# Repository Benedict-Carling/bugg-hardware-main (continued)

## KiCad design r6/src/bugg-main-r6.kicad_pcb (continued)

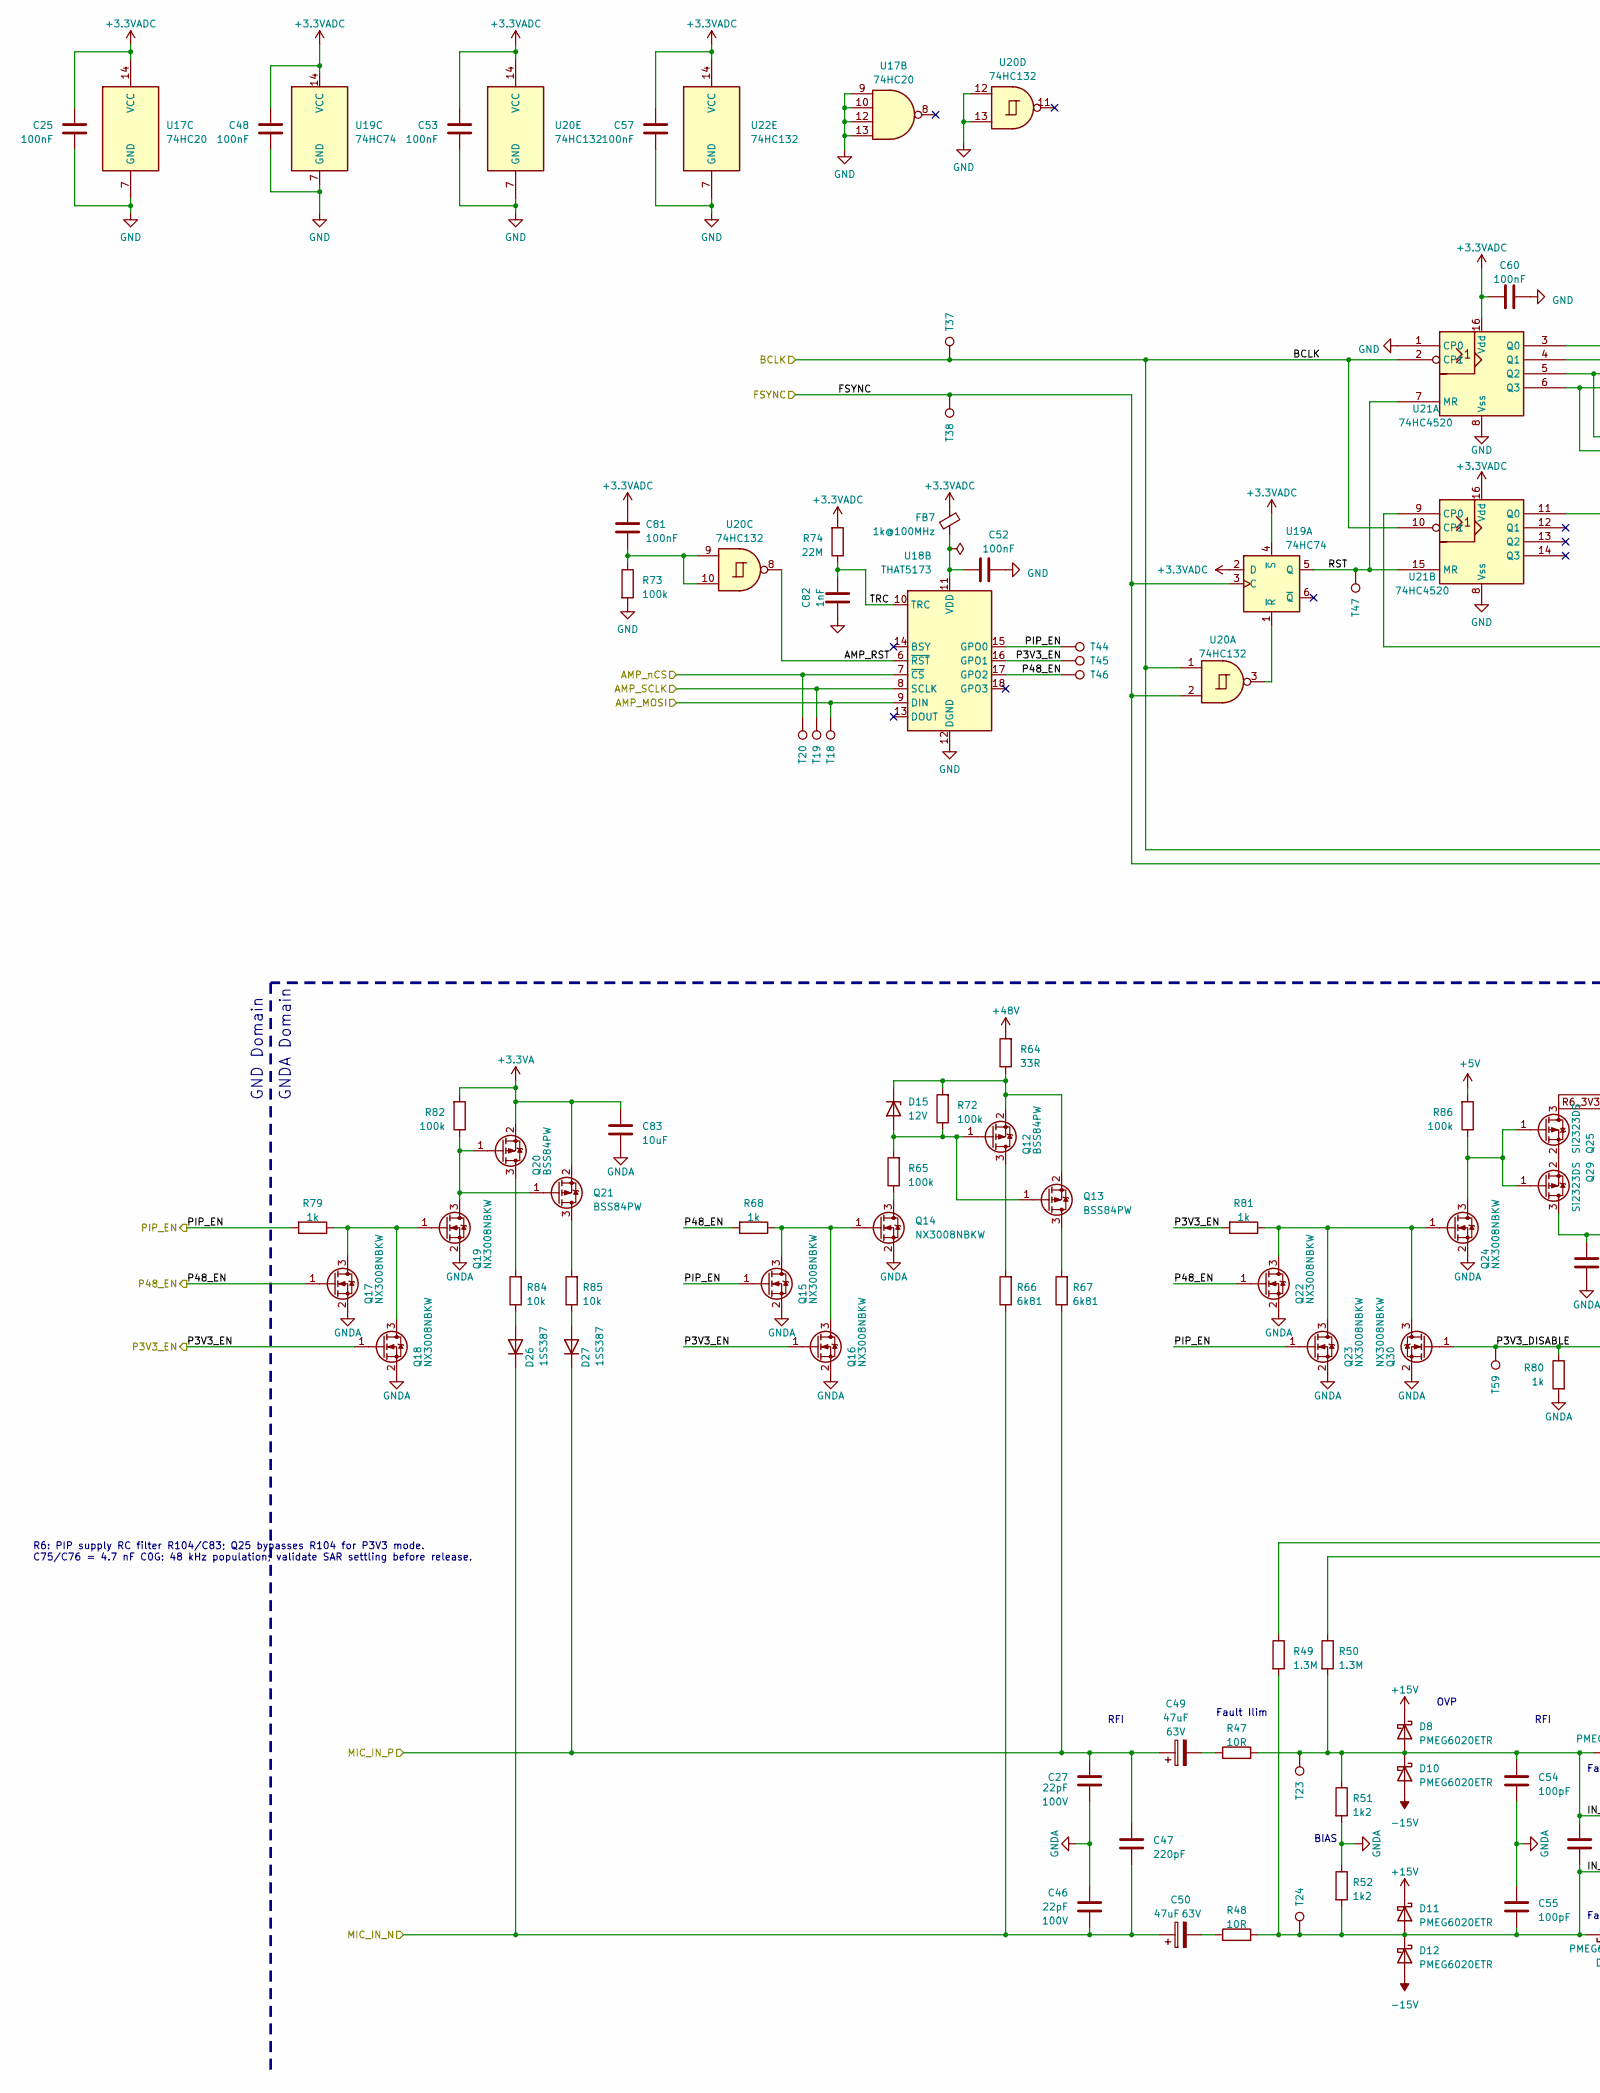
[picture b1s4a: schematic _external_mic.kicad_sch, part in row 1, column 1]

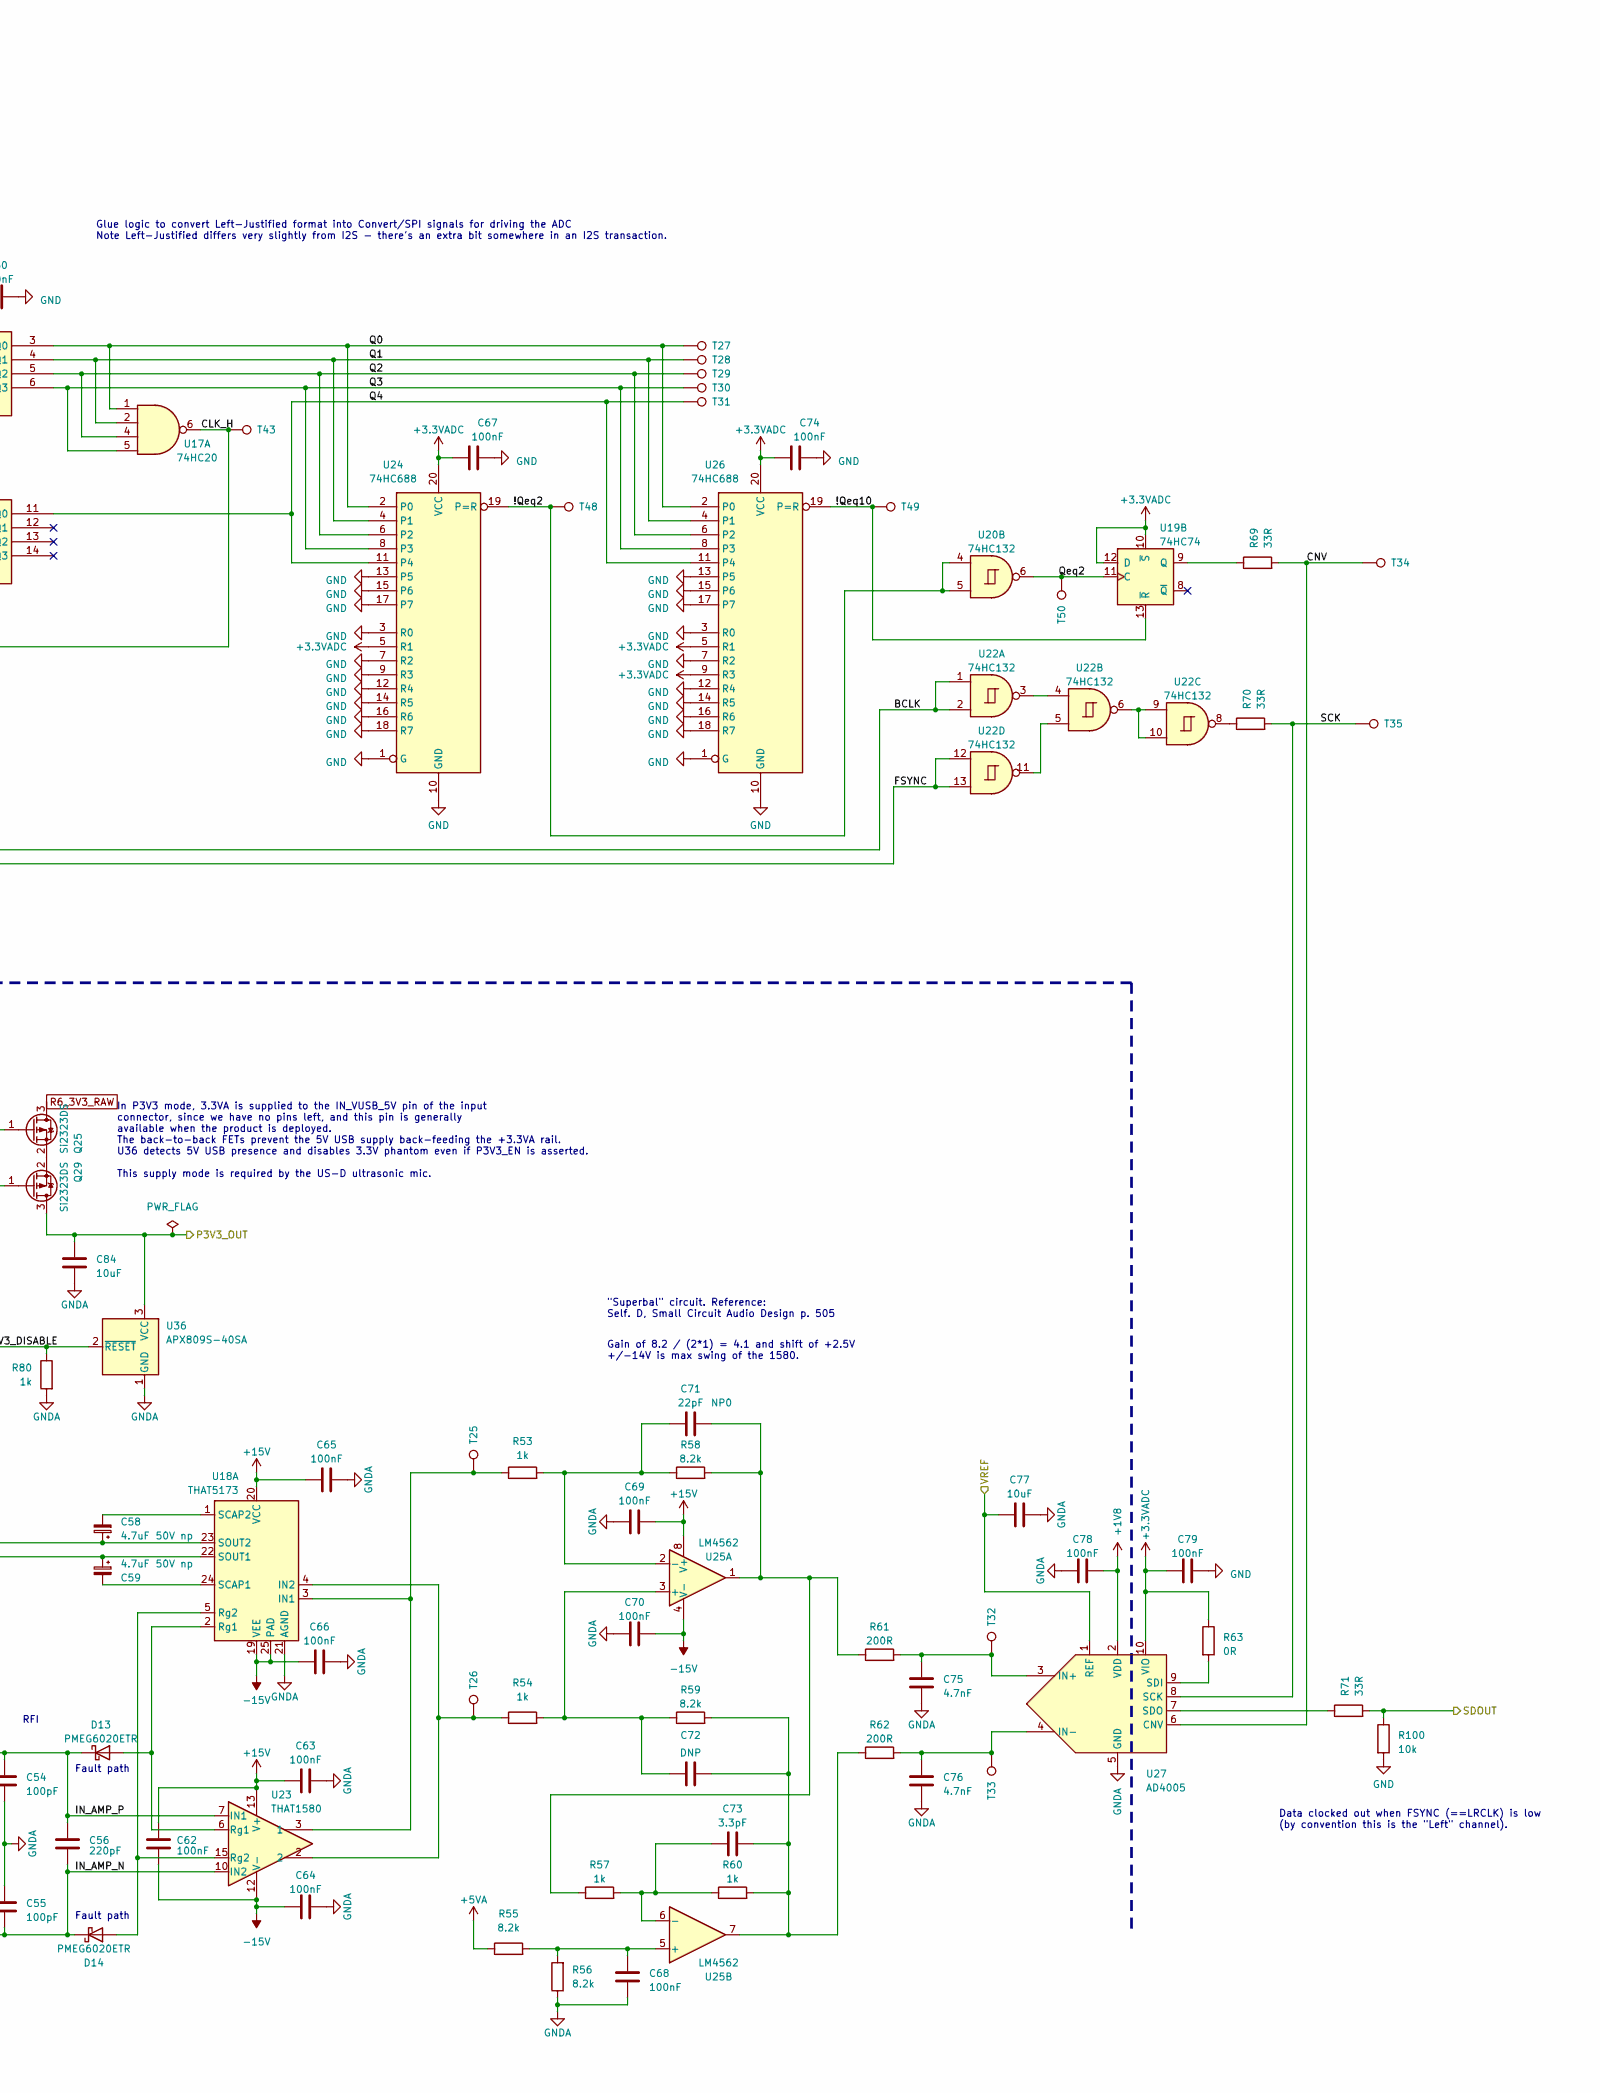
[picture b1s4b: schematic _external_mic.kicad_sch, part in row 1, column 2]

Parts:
C25, C48, C52, C53, C57, C60, C62, C63, C64, C65, C66, C67, C68, C69, C70, C74, C78, C79, C81: 100nF; C_0402_1005Metric; Voltage 50V; MPN GRM155R71H104KE14D; Mouser 81-GRM155R71H104KE4D
C27, C46, C71: 22pF; C_0402_1005Metric; Voltage 100V
C47, C56: 220pF; C_0402_1005Metric
C49, C50: 47uF; CP_Elec_8x10.5; Voltage 63V; MPN EMVH630ADA470MHA0G; Mouser 565-4268-1-ND
C54, C55: 100pF; C_0402_1005Metric
C58, C59: 4.7uF; CP_Elec_5x5.4; Voltage 50V np; MPN 865250642008; Mouser 710-865250642008
C72: DNP; C_0402_1005Metric
C73: 3.3pF; C_0402_1005Metric
C75, C76: 4.7nF; C_0402_1005Metric; MPN GRM1555C1H472JE01D
C77, C83, C84: 10uF; C_0603_1608Metric; Voltage 6.3V; MPN CL10A106MQ8NNNC; Mouser 187-CL10A106MQ8NNNC
C82: 1nF; C_0402_1005Metric
D8, D10, D11, D12, D13, D14: PMEG6020ETR; Nexperia_CFP3_SOD-123W; MPN PMEG6020ETR,115; Digikey 1727-1347-1-ND
D15: 12V; D_SOD-123; MPN BZT52C12-13-F; Digikey BZT52C1213-FDIDKR-ND
D26, D27: 1SS387; D_SOD-523; MPN 1SS387,L3F; Mouser 757-1SS387L3F
FB7: 1k@100MHz; L_0603_1608Metric; MPN BLM18KG102SN1D; Digikey 490-17349-1-ND
Q12, Q13, Q20, Q21: BSS84PW; SOT-323_SC-70; MPN BSS84PW; Mouser 726-BSS84PWH6327XTSA
Q14, Q15, Q16, Q17, Q18, Q19, Q22, Q23, Q24, Q30: NX3008NBKW; SOT-323_SC-70; MPN NX3008NBKW; Digikey 1727-1280-6-ND
Q25, Q29: Si2323DS; SOT-23; MPN SI2323DS-T1
R47, R48: 10R; R_1206_3216Metric; Tolerance 0.1%
R49, R50: 1.3M; R_0402_1005Metric
R51, R52: 1k2; R_0402_1005Metric; Tolerance 0.1% thin film; MPN ERA-2AEB122X; Mouser 667-ERA-2AEB122X
R53, R54, R57, R60: 1k; R_0402_1005Metric; Tolerance 0.1% thin film; MPN ERA-2AEB102X; Mouser 667-ERA-2AEB102X
R55, R56, R58, R59: 8.2k; R_0402_1005Metric; Tolerance 0.1% thin film; MPN ERA-2AEB822X; Mouser 667-ERA-2AEB822X
R61, R62: 200R; R_0402_1005Metric; Tolerance 0.1% thin film; MPN ERA-2AEB201X; Mouser 667-ERA-2AEB201X
R63: 0R; R_0402_1005Metric
R64, R69, R70, R71: 33R; R_0402_1005Metric
R65, R72, R73, R82, R86: 100k; R_0402_1005Metric
R66, R67: 6k81; R_1206_3216Metric
R68, R79, R80, R81: 1k; R_0402_1005Metric
R74: 22M; R_0402_1005Metric
R84, R85, R100: 10k; R_0402_1005Metric
T18, T19, T20, T23, T24, T25, T26, T27, T28, T29, T30, T31, T32, T33, T34, T35, T37, T38, T43, T44, T45, T46, T47, T48, T49, T50, T59: TestPoint_Pad_D1.0mm
U17: 74HC20; TSSOP-14_4.4x5mm_P0.65mm; MPN 74HC20PW; Mouser 771-HC20PW118
U18: THAT5173; QFN-24-1EP_5x5mm_P0.65mm_EP3.4x3.4mm_ThermalVias; MPN 5173N24-U; Mouser 887-5173N24-U
U19: 74HC74; TSSOP-14_4.4x5mm_P0.65mm; MPN 74HC74PW; Mouser 771-74HC74PW-T
U20, U22: 74HC132; TSSOP-14_4.4x5mm_P0.65mm; MPN 74HC132PW; Mouser 771-74HC132PW-T
U21: 74HC4520; TSSOP-16_4.4x5mm_P0.65mm; MPN 74HC4520PW; Mouser 771-HC4520PW118
U23: THAT1580; QFN-16-1EP_4x4mm_P0.65mm_EP2.1x2.1mm_ThermalVias; MPN 1580N16-U; Mouser 887-1580N16-U
U24, U26: 74HC688; TSSOP-20_4.4x6.5mm_P0.65mm; MPN 74HC688PW; Mouser 771-HC688PW118
U25: LM4562; SOIC-8_3.9x4.9mm_P1.27mm; MPN LM4562MA; Mouser 926-LM4562MAX/NOPB
U27: AD4005; MSOP-10_3x3mm_P0.5mm; MPN AD4005BRMZ; Mouser 584-AD4005BRMZ
U36: APX809S-40SA; SOT-23; MPN APX809S-40SA; Mouser 621-APX809S-40SA-7

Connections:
+1V8: C78.2, U27.2 (VDD); also elsewhere on the board
+3.3VA: C83.2, Q20.2 (S), Q21.2 (S), R82.2; also elsewhere on the board
+3.3VADC: C25.2, C48.2, C53.2, C57.2, C60.2, C67.2, C74.2, C79.2, C81.1, FB7.2, R63.1, R74.2, U17.14 (VCC), U19.2 (D), U19.4 (~S), U19.10 (~S), U19.12 (D), U19.14 (VCC), U20.14 (VCC), U21.16 (Vdd), U22.14 (VCC), U24.5 (R1), U24.20 (VCC), U26.5 (R1), U26.9 (R3), U26.20 (VCC), U27.10 (VIO); also elsewhere on the board
+5V: R86.2; also elsewhere on the board
+5VA: R55.1; also elsewhere on the board
+15V: C62.1, C63.2, C65.2, C69.2, D8.1 (K), D11.1 (K), U18.20 (VCC), U23.13 (V+), U25.8 (V+); also elsewhere on the board
+48V: R64.2; also elsewhere on the board
-15V: C62.2, C64.1, C66.2, C70.1, D10.2 (A), D12.2 (A), U18.19 (VEE), U18.25 (PAD), U23.12 (V-), U23.17 (V-), U25.4 (V-); also elsewhere on the board
/48V_EN: Q17.1 (G), Q22.1 (G), R68.2, T46.1, U18.17 (GPO2); also elsewhere on the board
/BCLK: T37.1, U20.1, U21.2 (CP1), U21.10 (CP1), U22.1, U22.2; also elsewhere on the board
/External Microphone Interface/!Qeq2: T48.1, U20.4, U20.5, U24.19 (P=R)
/External Microphone Interface/!Qeq10: T49.1, U19.13 (~R), U26.19 (P=R)
/External Microphone Interface/AMP_MOSI: T18.1, U18.9 (DIN); also elsewhere on the board
/External Microphone Interface/AMP_RST: U18.6 (~RST), U20.8
/External Microphone Interface/AMP_SCLK: T19.1, U18.8 (SCLK); also elsewhere on the board
/External Microphone Interface/AMP_nCS: T20.1, U18.7 (~CS); also elsewhere on the board
/External Microphone Interface/CLK_H: T43.1, U17.6, U21.9 (CP0)
/External Microphone Interface/CNV: R69.2, T34.1, U27.6 (CNV)
/External Microphone Interface/IN_AMP_N: C55.1, C56.1, D11.2 (A), D12.1 (K), D14.1 (K), R48.2, R49.2, R52.2, T24.1, U23.10 (IN2)
/External Microphone Interface/IN_AMP_P: C54.2, C56.2, D8.2 (A), D10.1 (K), D13.1 (K), R47.2, R50.2, R51.1, T23.1, U23.7 (IN1)
/External Microphone Interface/P3V3_DISABLE: Q30.1 (G), R80.1, T59.1, U36.2 (~RESET)
/External Microphone Interface/P3V3_EN: Q16.1 (G), Q18.1 (G), R81.2, T45.1, U18.16 (GPO1)
/External Microphone Interface/PIP_EN: Q15.1 (G), Q23.1 (G), R79.2, T44.1, U18.15 (GPO0)
/External Microphone Interface/Q0: T27.1, U17.1, U21.3 (Q0), U24.2 (P0), U26.2 (P0)
/External Microphone Interface/Q1: T28.1, U17.2, U21.4 (Q1), U24.4 (P1), U26.4 (P1)
/External Microphone Interface/Q2: T29.1, U17.4, U21.5 (Q2), U24.6 (P2), U26.6 (P2)
/External Microphone Interface/Q3: T30.1, U17.5, U21.6 (Q3), U24.8 (P3), U26.8 (P3)
/External Microphone Interface/Q4: T31.1, U21.11 (Q0), U24.11 (P4), U26.11 (P4)
/External Microphone Interface/Qeq2: T50.1, U19.11 (C), U20.6
/External Microphone Interface/RST: T47.1, U19.5 (Q), U21.7 (MR), U21.15 (MR)
/External Microphone Interface/SCK: R70.2, T35.1, U27.8 (SCK)
/External Microphone Interface/TRC: C82.2, R74.1, U18.10 (TRC)
/FSYNC: T38.1, U19.3 (C), U20.2, U22.12, U22.13; also elsewhere on the board
/MIC_IN_N: C46.1, C47.1, C50.1, D26.1 (K), R66.1; also elsewhere on the board
/MIC_IN_P: C27.2, C47.2, C49.1, D27.1 (K), R67.1; also elsewhere on the board
/P3V3_OUT: C84.2, Q29.3 (D), U36.3 (VCC); also elsewhere on the board
/SDOUT_EXT_MIC: R71.2, R100.1; also elsewhere on the board
/VREF: C77.2, U27.1 (REF); also elsewhere on the board
GND: C25.1, C48.1, C52.1, C53.1, C57.1, C60.1, C67.1, C74.1, C79.1, C82.1, R73.2, R100.2, U17.7 (GND), U17.9, U17.10, U17.12, U17.13, U18.12 (DGND), U19.7 (GND), U20.7 (GND), U20.12, U20.13, U21.1 (CP0), U21.8 (Vss), U22.7 (GND), U24.1 (G), U24.3 (R0), U24.7 (R2), U24.9 (R3), U24.10 (GND), U24.12 (R4), U24.13 (P5), U24.14 (R5), U24.15 (P6), U24.16 (R6), U24.17 (P7), U24.18 (R7), U26.1 (G), U26.3 (R0), U26.7 (R2), U26.10 (GND), U26.12 (R4), U26.13 (P5), U26.14 (R5), U26.15 (P6), U26.16 (R6), U26.17 (P7), U26.18 (R7); also elsewhere on the board
GNDA: C27.1, C46.2, C54.1, C55.2, C63.1, C64.2, C65.1, C66.1, C68.2, C69.1, C70.2, C75.2, C76.2, C77.1, C78.1, C83.1, C84.1, Q14.2 (S), Q15.2 (S), Q16.2 (S), Q17.2 (S), Q18.2 (S), Q19.2 (S), Q22.2 (S), Q23.2 (S), Q24.2 (S), Q30.2 (S), R51.2, R52.1, R56.1, R80.2, U18.21 (AGND), U27.5 (GND), U36.1 (GND); also elsewhere on the board
unnamed: C49.2, R47.1
unnamed: C50.2, R48.1
unnamed: C71.2, R57.1, R58.2, R61.1, U25.1
unnamed: C72.2, C73.2, R59.2, R60.2, R62.1, U25.7
unnamed: C81.2, R73.1, U20.9, U20.10
unnamed: D13.2 (A), U18.2 (Rg1), U23.6 (Rg1)
unnamed: D14.2 (A), U18.5 (Rg2), U23.15 (Rg2)
unnamed: D15.2 (A), Q12.1 (G), Q13.1 (G), R65.2, R72.1
unnamed: D15.1 (K), Q12.2 (S), Q13.2 (S), R64.1, R72.2
unnamed: D26.2 (A), R84.1
unnamed: D27.2 (A), R85.1
unnamed: Q12.3 (D), R66.2
unnamed: Q13.3 (D), R67.2
unnamed: Q14.3 (D), R65.1
unnamed: Q14.1 (G), Q15.3 (D), Q16.3 (D), R68.1
unnamed: Q17.3 (D), Q18.3 (D), Q19.1 (G), R79.1
unnamed: Q19.3 (D), Q20.1 (G), Q21.1 (G), R82.1
unnamed: Q20.3 (D), R84.2
unnamed: Q21.3 (D), R85.2
unnamed: Q22.3 (D), Q23.3 (D), Q24.1 (G), Q30.3 (D), R81.1
unnamed: Q24.3 (D), Q25.1 (G), Q29.1 (G), R86.1
unnamed: Q25.2 (S), Q29.2 (S)
unnamed: R70.1, U22.8
unnamed: R53.1, T25.1, U18.3 (IN1), U23.3 (1)
unnamed: R54.1, T26.1, U18.4 (IN2), U23.2
unnamed: C59.2, U18.24 (SCAP1)
unnamed: C58.2, U18.1 (SCAP2)
unnamed: C59.1, R50.1, U18.22 (SOUT1)
unnamed: C58.1, R49.1, U18.23 (SOUT2)
unnamed: C52.2, FB7.1, U18.11 (VDD)
unnamed: U19.1 (~R), U20.3
unnamed: R69.1, U19.9 (Q)
unnamed: U22.3, U22.4
unnamed: U22.6, U22.9, U22.10
unnamed: U22.5, U22.11
unnamed: C72.1, R54.2, R59.1, U25.3 (+)
unnamed: C71.1, R53.2, R58.1, U25.2 (-)
unnamed: C68.1, R55.2, R56.2, U25.5 (+)
unnamed: C73.1, R57.2, R60.1, U25.6 (-)
unnamed: C75.1, R61.2, T32.1, U27.3 (IN+)
unnamed: C76.1, R62.2, T33.1, U27.4 (IN-)
unnamed: R63.2, U27.9 (SDI)
unnamed: R71.1, U27.7 (SDO)
R6_3V3_RAW: Q25.3 (D); also elsewhere on the board

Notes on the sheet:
OVP
RFI
Fault path
BIAS
"Superbal" circuit. Reference: Self. D, Small Circuit Audio Design p. 505
Gain of 8.2 / (2*1) = 4.1 and shift of +2.5V +/-14V is max swing of the 1580.
Glue logic to convert Left-Justified format into Convert/SPI signals for driving the ADC Note Left-Justified differs very slightly from I2S - there's an extra bit somewhere in an I2S transaction.
Data clocked out when FSYNC (==LRCLK) is low (by convention this is the "Left" channel).
In P3V3 mode, 3.3VA is supplied to the IN_VUSB_5V pin of the input connector, since we have no pins left, and this pin is generally available when the product is deployed. The back-to-back FETs prevent the 5V USB supply back-feeding the +3.3VA rail. U36 detects 5V USB presence and disables 3.3V pha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
GNDA Domain
Fault Ilim
GND Domain
R6: PIP supply RC filter R104/C83; Q25 bypasses R104 for P3V3 mode. C75/C76 = 4.7 nF C0G: 48 kHz population; validate SAR settling before release.

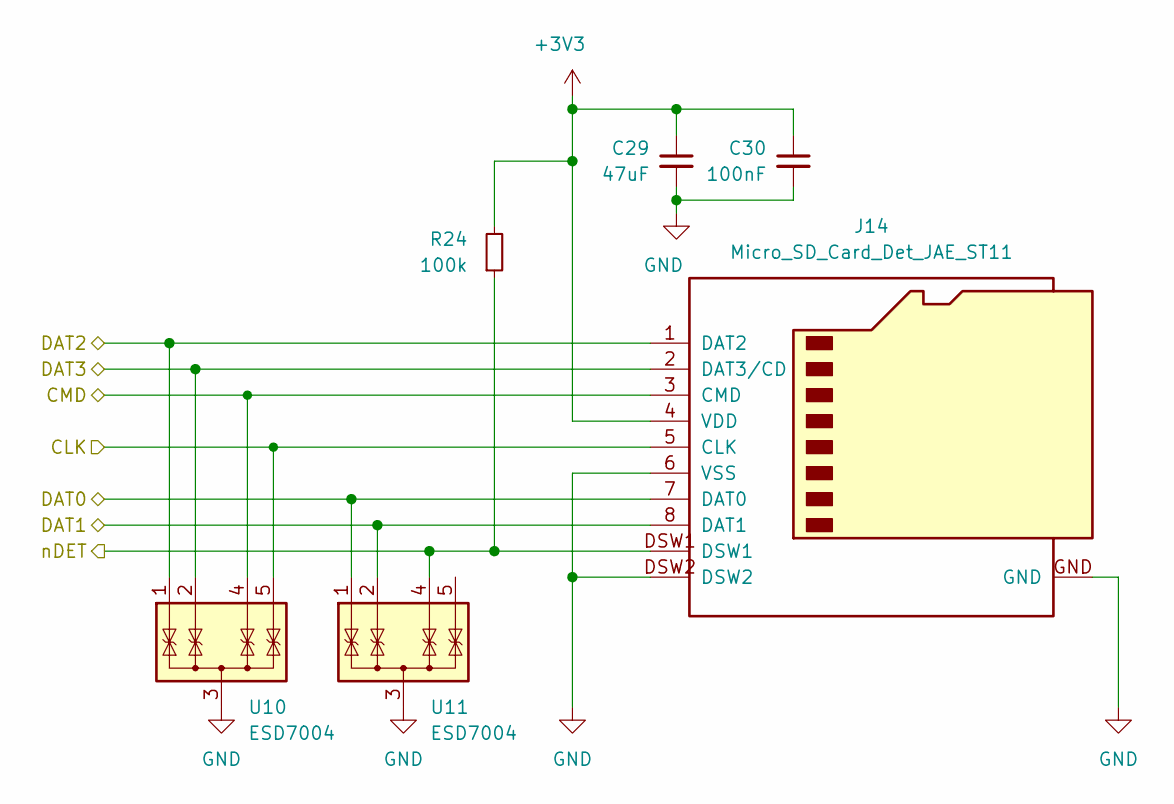
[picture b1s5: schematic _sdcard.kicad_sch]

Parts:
C29: 47uF; C_1206_3216Metric; Voltage 6.3V; MPN GRM31CE70J476ME15L; Mouser 81-GRM31CE70J476ME5L
C30: 100nF; C_0402_1005Metric; Voltage 50V; MPN GRM155R71H104KE14D; Mouser 81-GRM155R71H104KE4D
J14: Micro_SD_Card_Det_JAE_ST11; microSD_JAE_ST11S008V4H; MPN ST11S008V4HR2000; Digikey 670-2695-6-ND
R24: 100k; R_0402_1005Metric
U10, U11: ESD7004; USON-10_2.5x1.0mm_P0.5mm; MPN ESD7004MUTAG; Digikey ESD7004MUTAGOSDKR-ND

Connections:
+3V3: C29.1, C30.1, J14.4 (VDD), R24.2; also elsewhere on the board
/SD_CLK: J14.5 (CLK), U10.5 (IO4), U10.6; also elsewhere on the board
/SD_CMD: J14.3 (CMD), U10.4 (IO3), U10.7; also elsewhere on the board
/SD_DAT0: J14.7 (DAT0), U11.1 (IO1), U11.10; also elsewhere on the board
/SD_DAT1: J14.8 (DAT1), U11.2 (IO2), U11.9; also elsewhere on the board
/SD_DAT2: J14.1 (DAT2), U10.1 (IO1), U10.10; also elsewhere on the board
/SD_DAT3: J14.2 (DAT3/CD), U10.2 (IO2), U10.9; also elsewhere on the board
/SD_nDET: J14.DSW1, R24.1, U11.4 (IO3), U11.7; also elsewhere on the board
GND: C29.2, C30.2, J14.6 (VSS), J14.DSW2, J14.GND, U10.3 (G), U10.8, U11.3 (G), U11.8; also elsewhere on the board
unnamed: U11.5 (IO4), U11.6

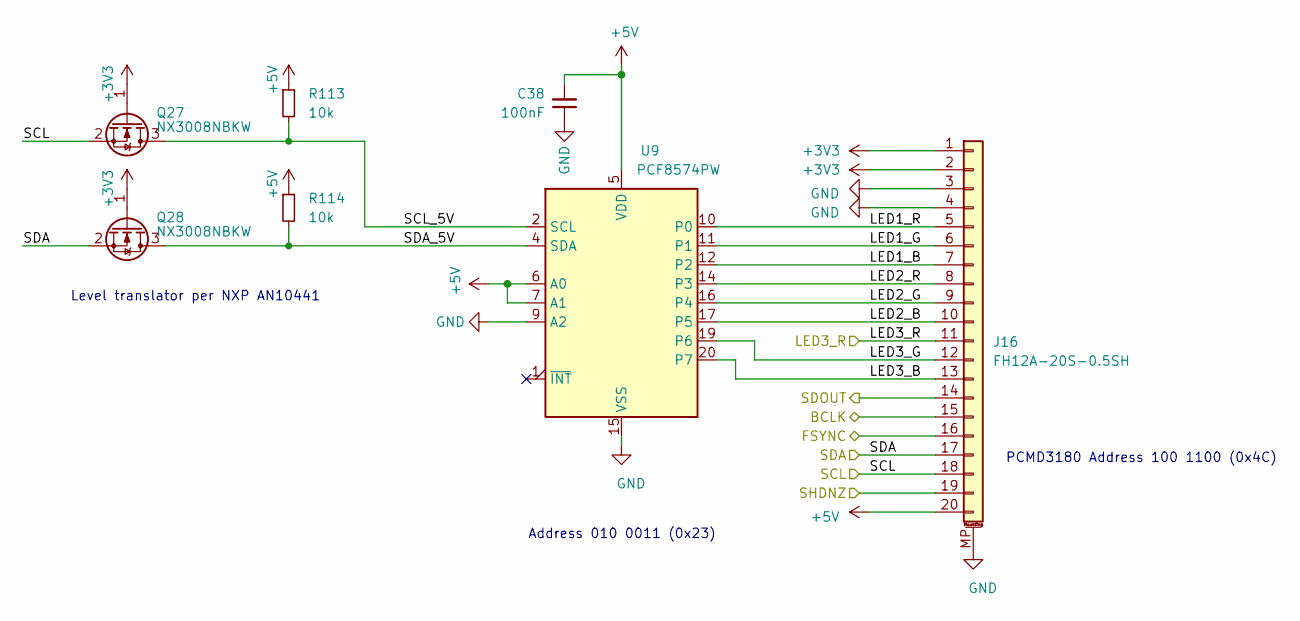
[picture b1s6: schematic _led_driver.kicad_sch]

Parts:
C38: 100nF; C_0402_1005Metric; Voltage 50V; MPN GRM155R71H104KE14D; Mouser 81-GRM155R71H104KE4D
J16: FH12A-20S-0.5SH; Hirose_FH12-20S-0.5SH_1x20-1MP_P0.50mm_Horizontal; MPN FH12A-20S-0.5SH(55); Digikey HFK120CT-ND
Q27, Q28: NX3008NBKW; SOT-323_SC-70; MPN NX3008NBKW; Digikey 1727-1280-6-ND
R113, R114: 10k; R_0402_1005Metric
U9: PCF8574PW; SSOP-20_4.4x6.5mm_P0.65mm; MPN PCF8574PW; Digikey TI

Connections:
+3V3: J16.1, J16.2, Q27.1 (G), Q28.1 (G); also elsewhere on the board
+5V: C38.2, J16.20, R113.1, R114.1, U9.5 (VDD), U9.6 (A0), U9.7 (A1); also elsewhere on the board
/BCLK: J16.15; also elsewhere on the board
/FSYNC: J16.16; also elsewhere on the board
/LED driver, LED board connections/LED1_B: J16.7, U9.12 (P2)
/LED driver, LED board connections/LED1_G: J16.6, U9.11 (P1)
/LED driver, LED board connections/LED1_R: J16.5, U9.10 (P0)
/LED driver, LED board connections/LED2_B: J16.10, U9.17 (P5)
/LED driver, LED board connections/LED2_G: J16.9, U9.16 (P4)
/LED driver, LED board connections/LED2_R: J16.8, U9.14 (P3)
/LED driver, LED board connections/LED3_B: J16.13, U9.20 (P7)
/LED driver, LED board connections/LED3_G: J16.12, U9.19 (P6)
/LED driver, LED board connections/SCL_5V: Q27.3 (D), R113.2, U9.2 (SCL)
/LED driver, LED board connections/SDA_5V: Q28.3 (D), R114.2, U9.4 (SDA)
/SDOUT_INT_MIC: J16.14; also elsewhere on the board
/SHDNZ: J16.19; also elsewhere on the board
/nPWR_LED: J16.11; also elsewhere on the board
GND: C38.1, J16.3, J16.4, J16.MP (MountPin), U9.9 (A2), U9.15 (VSS); also elsewhere on the board
R6_SCL: J16.18, Q27.2 (S); also elsewhere on the board
R6_SDA: J16.17, Q28.2 (S); also elsewhere on the board

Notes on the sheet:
Level translator per NXP AN10441
PCMD3180 Address 100 1100 (0x4C)
Address 010 0011 (0x23)

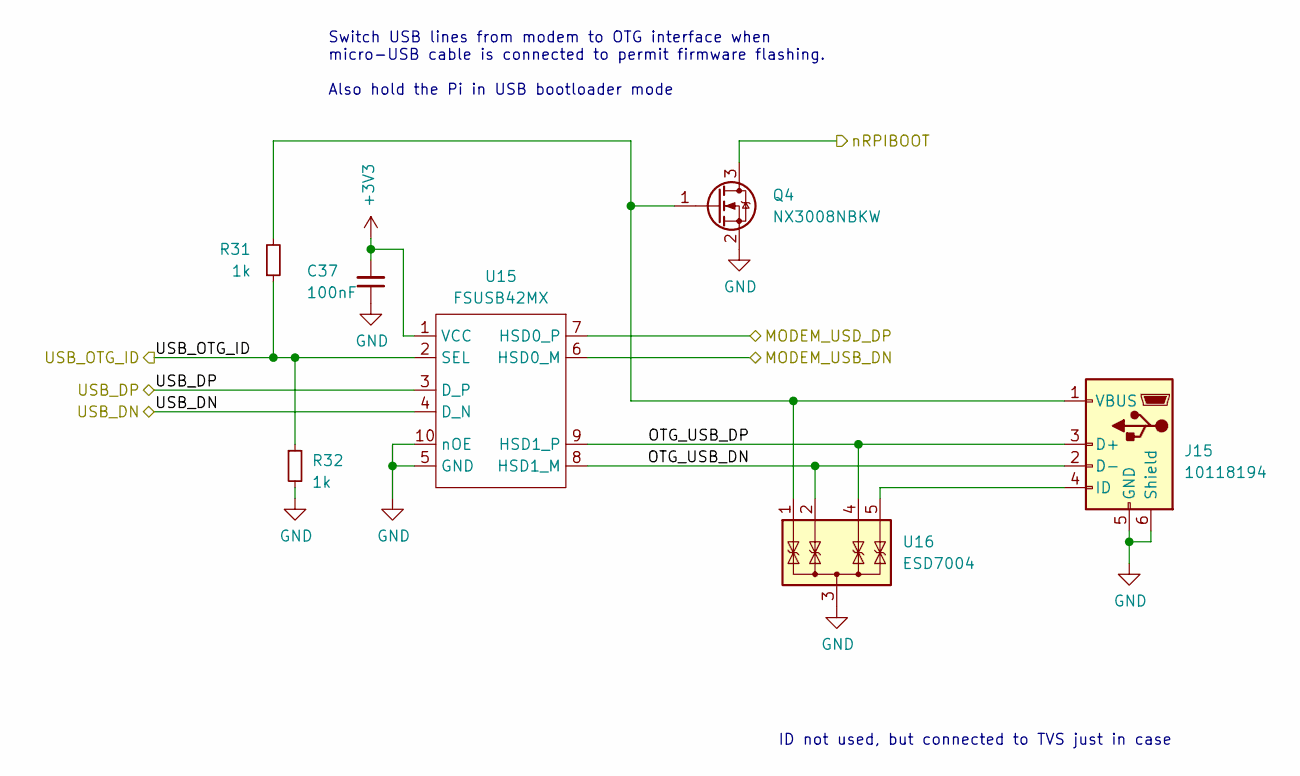
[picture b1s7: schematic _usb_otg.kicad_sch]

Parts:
C37: 100nF; C_0402_1005Metric; Voltage 50V; MPN GRM155R71H104KE14D; Mouser 81-GRM155R71H104KE4D
J15: 10118194; USB_Micro-B_Amphenol_10118194_Horizontal; MPN 10118194-0001LF; Digikey 609-4618-6-ND
Q4: NX3008NBKW; SOT-323_SC-70; MPN NX3008NBKW; Digikey 1727-1280-6-ND
R31, R32: 1k; R_0402_1005Metric
U15: FSUSB42MX; MSOP-10_3x3mm_P0.5mm; MPN FSUSB42MUX; Digikey FSUSB42MUXDKR-ND
U16: ESD7004; USON-10_2.5x1.0mm_P0.5mm; MPN ESD7004MUTAG; Digikey ESD7004MUTAGOSDKR-ND

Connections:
+3V3: C37.2, U15.1 (VCC); also elsewhere on the board
/MODEM_USB_DN: U15.6 (HSD0_M); also elsewhere on the board
/MODEM_USB_DP: U15.7 (HSD0_P); also elsewhere on the board
/USB-OTG flashing interface/OTG_USB_DN: J15.2 (D-), U15.8 (HSD1_M), U16.2 (IO2), U16.9
/USB-OTG flashing interface/OTG_USB_DP: J15.3 (D+), U15.9 (HSD1_P), U16.4 (IO3), U16.7
/USB_DN: U15.4 (D_N); also elsewhere on the board
/USB_DP: U15.3 (D_P); also elsewhere on the board
/USB_OTG_ID: R31.1, R32.1, U15.2 (SEL); also elsewhere on the board
/nRPIBOOT: Q4.3 (D); also elsewhere on the board
GND: C37.1, J15.5 (GND), J15.6 (Shield), Q4.2 (S), R32.2, U15.5 (GND), U15.10 (nOE), U16.3 (G), U16.8; also elsewhere on the board
unnamed: J15.4 (ID), U16.5 (IO4), U16.6
unnamed: J15.1 (VBUS), Q4.1 (G), R31.2, U16.1 (IO1), U16.10

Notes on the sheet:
Switch USB lines from modem to OTG interface when micro-USB cable is connected to permit firmware flashing. Also hold the Pi in USB bootloader mode
ID not used, but connected to TVS just in case
